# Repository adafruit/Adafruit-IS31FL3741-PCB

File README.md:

## Adafruit IS31FL3741 13x9 PWM RGB LED Matrix Driver PCB

<a href="http://www.adafruit.com/products/5201"><br/>
Click here to purchase one from the Adafruit shop</a>

PCB files for the Adafruit IS31FL3741 13x9 PWM RGB LED Matrix Driver. 

Format is EagleCAD schematic and board layout
* https://www.adafruit.com/product/5201

### Description

Add a splash of RGB LEDs to a project you're working on, with this adorable 13x9 RGB LED matrix breakout. It features -- no surprise -- 117 RGB LEDs, each one 2x2mm in size, in a 13x9 grid with 3mm pitch spacing.

Unlike our 8x8 dotstar grid here, these are not NeoPixel or DotStar or other 'smart' RGB LEDs. Instead of having a lil chip in each LED, there's one large controller chip that handles all the PWM for you. The ISSI IS32FL3741 communicates over I2C and can set each LED element with 8 bit PWM for 24-bit color across the RGB elements, for beautiful color! There's an adjustable current driver so you can brighten or dim the whole display without losing color resolution.

Each assembled board comes with the grid, four mounting holes, and the IS31FL3741 chip with all supporting circuitry. The board can run from 3.3 to 5V DC power and logic - powering from 5V is recommended since the green and blue LEDs look better with the extra headroom. We designed the PCB so you can tile the boards side-to-side if you desire, you'll just have to cut/solder the jumpers on the bottom to change the I2C address: Up to 4 boards can share one I2C bus.

Use Arduino or CircuitPython/Python to quickly set pixels to any color you desire. Note that I2C makes this board very easy to wire up compared to our "HUB75"-style RGB LED Matrices but that also makes the display slower because each pixel must be written over I2C. For a small display with simple animations, its fine - but if you want to do video or larger graphics we recommend upgrading to the HUB75 style.

We made it easy for you to get some color right into your next project. The LED matrix and circuitry is soldered onto a custom-made PCB with two STEMMA QT connectors on the top, and are compatible with the SparkFun Qwiic I2C connectors. This allows you to make solderless connections between your development board and the IS31FL3741 or to chain it with a wide range of other sensors and accessories using a compatible cable.

### License

Adafruit invests time and resources providing this open source design, please support Adafruit and open-source hardware by purchasing products from [Adafruit](https://www.adafruit.com)!

Designed by Limor Fried/Ladyada for Adafruit Industries.

Creative Commons Attribution/Share-Alike, all text above must be included in any redistribution. 
See license.txt for additional details.

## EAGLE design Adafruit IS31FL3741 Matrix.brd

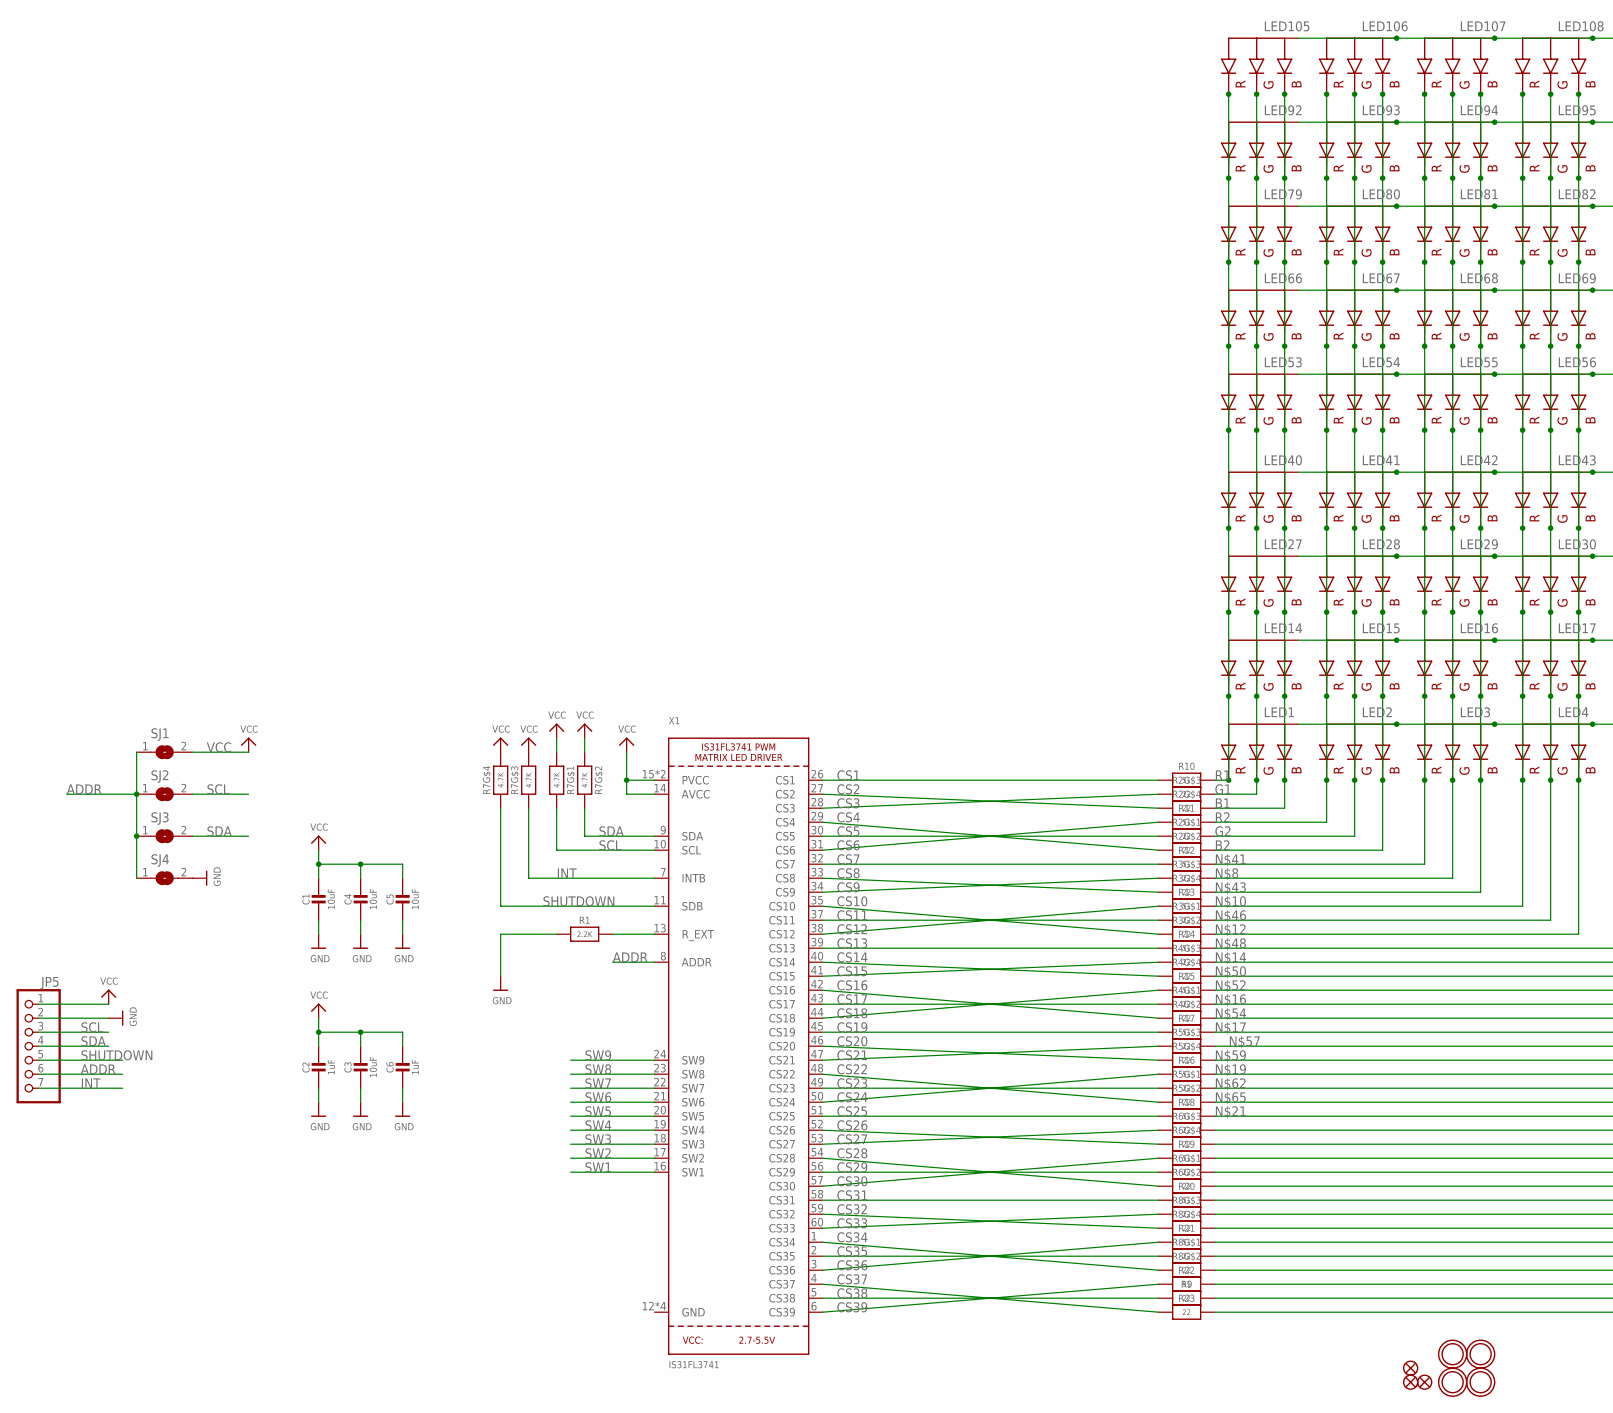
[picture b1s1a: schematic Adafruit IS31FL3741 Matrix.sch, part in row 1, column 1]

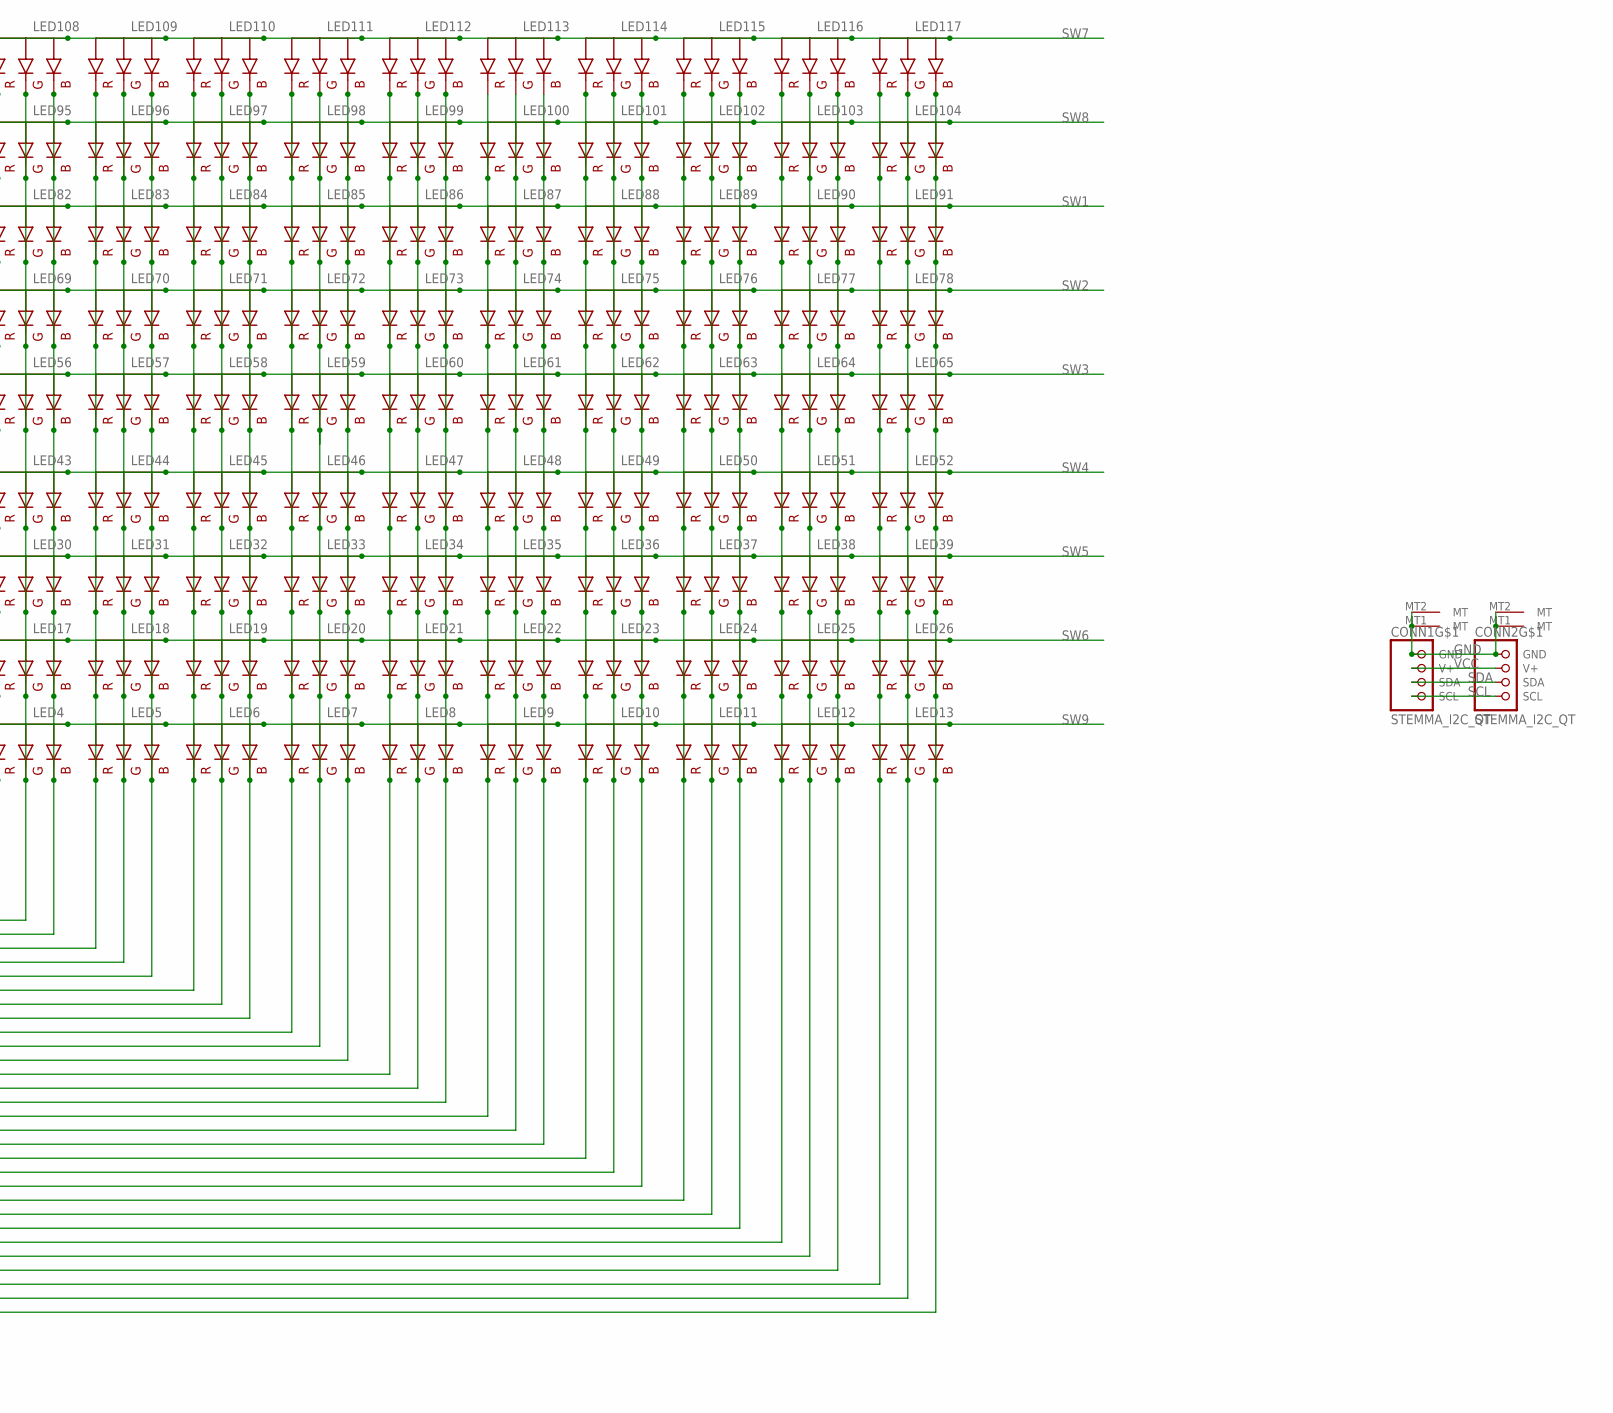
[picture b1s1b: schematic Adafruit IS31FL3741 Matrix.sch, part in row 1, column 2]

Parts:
C1, C3, C4, C5: 10uF; 0805-NO
C2, C6: 1uF; 0603-NO
CONN1, CONN2: STEMMA_I2C_QT; JST_SH4
FID1, FID2, FID3: FIDUCIAL_1MM
JP5: HEADER-1X7THICKER; 1X07_ROUND_76
LED1, LED2, LED3, LED4, LED5, LED6, LED7, LED8, LED9, LED10, LED11, LED12, LED13, LED14, LED15, LED16, LED17, LED18, LED19, LED20, LED21, LED22, LED23, LED24, LED25, LED26, LED27, LED28, LED29, LED30, LED31, LED32, LED33, LED34, LED35, LED36, LED37, LED38, LED39, LED40, LED41, LED42, LED43, LED44, LED45, LED46, LED47, LED48, LED49, LED50, LED51, LED52, LED53, LED54, LED55, LED56, LED57, LED58, LED59, LED60, LED61, LED62, LED63, LED64, LED65, LED66, LED67, LED68, LED69, LED70, LED71, LED72, LED73, LED74, LED75, LED76, LED77, LED78, LED79, LED80, LED81, LED82, LED83, LED84, LED85, LED86, LED87, LED88, LED89, LED90, LED91, LED92, LED93, LED94, LED95, LED96, LED97, LED98, LED99, LED100, LED101, LED102, LED103, LED104, LED105, LED106, LED107, LED108, LED109, LED110, LED111, LED112, LED113, LED114, LED115, LED116, LED117: RGBLED_CA_2121; RGBLED_2121
R1: 2.2K; 0603-NO
R2, R3, R4, R5, R6, R8: 22; RESPACK_4X0603
R7: 4.7K; RESPACK_4X0603
R9, R23: 22; 0603-NO
R10, R11, R12, R13, R14, R15, R16, R17, R18, R19, R20, R21, R22: 51; 0603-NO
SJ1, SJ2, SJ3: SOLDERJUMPER; SOLDERJUMPER_ARROW_NOPASTE
SJ4: SOLDERJUMPERCLOSED; SOLDERJUMPER_CLOSEDWIRE
U$3, U$4, U$5, U$6: MOUNTINGHOLE2.5; MOUNTINGHOLE_2.5_PLATED
X1: IS31FL3741; QFN60_7MM

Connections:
ADDR: JP5.6, SJ1.1, SJ2.1, SJ3.1, SJ4.1, X1.8 (ADDR)
B1: LED1.B (BLUE), LED14.B (BLUE), LED27.B (BLUE), LED40.B (BLUE), LED53.B (BLUE), LED66.B (BLUE), LED79.B (BLUE), LED92.B (BLUE), LED105.B (BLUE), R2.5 (2)
B2: LED2.B (BLUE), LED15.B (BLUE), LED28.B (BLUE), LED41.B (BLUE), LED54.B (BLUE), LED67.B (BLUE), LED80.B (BLUE), LED93.B (BLUE), LED106.B (BLUE), R2.7 (2)
CS1: R10.1, X1.26 (CS1)
CS2: R2.4 (1), X1.27 (CS2)
CS3: R2.3 (1), X1.28 (CS3)
CS4: R2.2 (1), X1.29 (CS4)
CS5: R2.1, X1.30 (CS5)
CS6: R11.1, X1.31 (CS6)
CS7: R12.1, X1.32 (CS7)
CS8: R3.4 (1), X1.33 (CS8)
CS9: R3.3 (1), X1.34 (CS9)
CS10: R3.2 (1), X1.35 (CS10)
CS11: R3.1, X1.37 (CS11)
CS12: R13.1, X1.38 (CS12)
CS13: R14.1, X1.39 (CS13)
CS14: R4.4 (1), X1.40 (CS14)
CS15: R4.3 (1), X1.41 (CS15)
CS16: R4.2 (1), X1.42 (CS16)
CS17: R4.1, X1.43 (CS17)
CS18: R15.1, X1.44 (CS18)
CS19: R17.1, X1.45 (CS19)
CS20: R5.4 (1), X1.46 (CS20)
CS21: R5.3 (1), X1.47 (CS21)
CS22: R5.2 (1), X1.48 (CS22)
CS23: R5.1, X1.49 (CS23)
CS24: R16.1, X1.50 (CS24)
CS25: R18.1, X1.51 (CS25)
CS26: R6.4 (1), X1.52 (CS26)
CS27: R6.3 (1), X1.53 (CS27)
CS28: R6.2 (1), X1.54 (CS28)
CS29: R6.1, X1.56 (CS29)
CS30: R19.1, X1.57 (CS30)
CS31: R20.1, X1.58 (CS31)
CS32: R8.4 (1), X1.59 (CS32)
CS33: R8.3 (1), X1.60 (CS33)
CS34: R8.2 (1), X1.1 (CS34)
CS35: R8.1, X1.2 (CS35)
CS36: R21.1, X1.3 (CS36)
CS37: R23.1, X1.4 (CS37)
CS38: R9.1, X1.5 (CS38)
CS39: R22.1, X1.6 (CS39)
G1: LED1.G (GREEN), LED14.G (GREEN), LED27.G (GREEN), LED40.G (GREEN), LED53.G (GREEN), LED66.G (GREEN), LED79.G (GREEN), LED92.G (GREEN), LED105.G (GREEN), R2.6 (2)
G2: LED2.G (GREEN), LED15.G (GREEN), LED28.G (GREEN), LED41.G (GREEN), LED54.G (GREEN), LED67.G (GREEN), LED80.G (GREEN), LED93.G (GREEN), LED106.G (GREEN), R2.8 (2)
GND: C1.2, C2.2, C3.2, C4.2, C5.2, C6.2, CONN1.1 (GND), CONN1.MT1 (MT), CONN1.MT2 (MT), CONN2.1 (GND), CONN2.MT1 (MT), CONN2.MT2 (MT), JP5.2, R1.1, SJ4.2, X1.12 (GND), X1.36 (GND), X1.55 (GND), X1.THERMAL (GND)
INT: JP5.7, R7.3 (1), X1.7 (INTB)
unnamed: R1.2, X1.13 (R_EXT)
unnamed: LED3.G (GREEN), LED16.G (GREEN), LED29.G (GREEN), LED42.G (GREEN), LED55.G (GREEN), LED68.G (GREEN), LED81.G (GREEN), LED94.G (GREEN), LED107.G (GREEN), R3.6 (2)
unnamed: LED4.R (RED), LED17.R (RED), LED30.R (RED), LED43.R (RED), LED56.R (RED), LED69.R (RED), LED82.R (RED), LED95.R (RED), LED108.R (RED), R13.2
unnamed: LED4.B (BLUE), LED17.B (BLUE), LED30.B (BLUE), LED43.B (BLUE), LED56.B (BLUE), LED69.B (BLUE), LED82.B (BLUE), LED95.B (BLUE), LED108.B (BLUE), R3.7 (2)
unnamed: LED5.G (GREEN), LED18.G (GREEN), LED31.G (GREEN), LED44.G (GREEN), LED57.G (GREEN), LED70.G (GREEN), LED83.G (GREEN), LED96.G (GREEN), LED109.G (GREEN), R4.6 (2)
unnamed: LED6.G (GREEN), LED19.G (GREEN), LED32.G (GREEN), LED45.G (GREEN), LED58.G (GREEN), LED71.G (GREEN), LED84.G (GREEN), LED97.G (GREEN), LED110.G (GREEN), R4.8 (2)
unnamed: LED7.R (RED), LED20.R (RED), LED33.R (RED), LED46.R (RED), LED59.R (RED), LED72.R (RED), LED85.R (RED), LED98.R (RED), LED111.R (RED), R17.2
unnamed: LED8.R (RED), LED21.R (RED), LED34.R (RED), LED47.R (RED), LED60.R (RED), LED73.R (RED), LED86.R (RED), LED99.R (RED), LED112.R (RED), R16.2
unnamed: LED9.R (RED), LED22.R (RED), LED35.R (RED), LED48.R (RED), LED61.R (RED), LED74.R (RED), LED87.R (RED), LED100.R (RED), LED113.R (RED), R18.2
unnamed: LED9.B (BLUE), LED22.B (BLUE), LED35.B (BLUE), LED48.B (BLUE), LED61.B (BLUE), LED74.B (BLUE), LED87.B (BLUE), LED100.B (BLUE), LED113.B (BLUE), R6.5 (2)
unnamed: LED10.G (GREEN), LED23.G (GREEN), LED36.G (GREEN), LED49.G (GREEN), LED62.G (GREEN), LED75.G (GREEN), LED88.G (GREEN), LED101.G (GREEN), LED114.G (GREEN), R6.8 (2)
unnamed: LED11.R (RED), LED24.R (RED), LED37.R (RED), LED50.R (RED), LED63.R (RED), LED76.R (RED), LED89.R (RED), LED102.R (RED), LED115.R (RED), R20.2
unnamed: LED11.B (BLUE), LED24.B (BLUE), LED37.B (BLUE), LED50.B (BLUE), LED63.B (BLUE), LED76.B (BLUE), LED89.B (BLUE), LED102.B (BLUE), LED115.B (BLUE), R8.5 (2)
unnamed: LED12.G (GREEN), LED25.G (GREEN), LED38.G (GREEN), LED51.G (GREEN), LED64.G (GREEN), LED77.G (GREEN), LED90.G (GREEN), LED103.G (GREEN), LED116.G (GREEN), R8.8 (2)
unnamed: LED13.R (RED), LED26.R (RED), LED39.R (RED), LED52.R (RED), LED65.R (RED), LED78.R (RED), LED91.R (RED), LED104.R (RED), LED117.R (RED), R22.2
unnamed: LED13.B (BLUE), LED26.B (BLUE), LED39.B (BLUE), LED52.B (BLUE), LED65.B (BLUE), LED78.B (BLUE), LED91.B (BLUE), LED104.B (BLUE), LED117.B (BLUE), R23.2
unnamed: LED3.R (RED), LED16.R (RED), LED29.R (RED), LED42.R (RED), LED55.R (RED), LED68.R (RED), LED81.R (RED), LED94.R (RED), LED107.R (RED), R12.2
unnamed: LED3.B (BLUE), LED16.B (BLUE), LED29.B (BLUE), LED42.B (BLUE), LED55.B (BLUE), LED68.B (BLUE), LED81.B (BLUE), LED94.B (BLUE), LED107.B (BLUE), R3.5 (2)
unnamed: LED4.G (GREEN), LED17.G (GREEN), LED30.G (GREEN), LED43.G (GREEN), LED56.G (GREEN), LED69.G (GREEN), LED82.G (GREEN), LED95.G (GREEN), LED108.G (GREEN), R3.8 (2)
unnamed: LED5.R (RED), LED18.R (RED), LED31.R (RED), LED44.R (RED), LED57.R (RED), LED70.R (RED), LED83.R (RED), LED96.R (RED), LED109.R (RED), R14.2
unnamed: LED5.B (BLUE), LED18.B (BLUE), LED31.B (BLUE), LED44.B (BLUE), LED57.B (BLUE), LED70.B (BLUE), LED83.B (BLUE), LED96.B (BLUE), LED109.B (BLUE), R4.5 (2)
unnamed: LED6.R (RED), LED19.R (RED), LED32.R (RED), LED45.R (RED), LED58.R (RED), LED71.R (RED), LED84.R (RED), LED97.R (RED), LED110.R (RED), R15.2
unnamed: LED6.B (BLUE), LED19.B (BLUE), LED32.B (BLUE), LED45.B (BLUE), LED58.B (BLUE), LED71.B (BLUE), LED84.B (BLUE), LED97.B (BLUE), LED110.B (BLUE), R4.7 (2)
unnamed: LED7.G (GREEN), LED20.G (GREEN), LED33.G (GREEN), LED46.G (GREEN), LED59.G (GREEN), LED72.G (GREEN), LED85.G (GREEN), LED98.G (GREEN), LED111.G (GREEN), R5.6 (2)
unnamed: LED7.B (BLUE), LED20.B (BLUE), LED33.B (BLUE), LED46.B (BLUE), LED59.B (BLUE), LED72.B (BLUE), LED85.B (BLUE), LED98.B (BLUE), LED111.B (BLUE), R5.5 (2)
unnamed: LED8.G (GREEN), LED21.G (GREEN), LED34.G (GREEN), LED47.G (GREEN), LED60.G (GREEN), LED73.G (GREEN), LED86.G (GREEN), LED99.G (GREEN), LED112.G (GREEN), R5.8 (2)
unnamed: LED8.B (BLUE), LED21.B (BLUE), LED34.B (BLUE), LED47.B (BLUE), LED60.B (BLUE), LED73.B (BLUE), LED86.B (BLUE), LED99.B (BLUE), LED112.B (BLUE), R5.7 (2)
unnamed: LED9.G (GREEN), LED22.G (GREEN), LED35.G (GREEN), LED48.G (GREEN), LED61.G (GREEN), LED74.G (GREEN), LED87.G (GREEN), LED100.G (GREEN), LED113.G (GREEN), R6.6 (2)
unnamed: LED10.R (RED), LED23.R (RED), LED36.R (RED), LED49.R (RED), LED62.R (RED), LED75.R (RED), LED88.R (RED), LED101.R (RED), LED114.R (RED), R19.2
unnamed: LED10.B (BLUE), LED23.B (BLUE), LED36.B (BLUE), LED49.B (BLUE), LED62.B (BLUE), LED75.B (BLUE), LED88.B (BLUE), LED101.B (BLUE), LED114.B (BLUE), R6.7 (2)
unnamed: LED11.G (GREEN), LED24.G (GREEN), LED37.G (GREEN), LED50.G (GREEN), LED63.G (GREEN), LED76.G (GREEN), LED89.G (GREEN), LED102.G (GREEN), LED115.G (GREEN), R8.6 (2)
unnamed: LED12.R (RED), LED25.R (RED), LED38.R (RED), LED51.R (RED), LED64.R (RED), LED77.R (RED), LED90.R (RED), LED103.R (RED), LED116.R (RED), R21.2
unnamed: LED12.B (BLUE), LED25.B (BLUE), LED38.B (BLUE), LED51.B (BLUE), LED64.B (BLUE), LED77.B (BLUE), LED90.B (BLUE), LED103.B (BLUE), LED116.B (BLUE), R8.7 (2)
unnamed: LED13.G (GREEN), LED26.G (GREEN), LED39.G (GREEN), LED52.G (GREEN), LED65.G (GREEN), LED78.G (GREEN), LED91.G (GREEN), LED104.G (GREEN), LED117.G (GREEN), R9.2
R1: LED1.R (RED), LED14.R (RED), LED27.R (RED), LED40.R (RED), LED53.R (RED), LED66.R (RED), LED79.R (RED), LED92.R (RED), LED105.R (RED), R10.2
R2: LED2.R (RED), LED15.R (RED), LED28.R (RED), LED41.R (RED), LED54.R (RED), LED67.R (RED), LED80.R (RED), LED93.R (RED), LED106.R (RED), R11.2
SCL: CONN1.4 (SCL), CONN2.4 (SCL), JP5.3, R7.8 (2), SJ2.2, X1.10 (SCL)
SDA: CONN1.3 (SDA), CONN2.3 (SDA), JP5.4, R7.7 (2), SJ3.2, X1.9 (SDA)
SHUTDOWN: JP5.5, R7.4 (1), X1.11 (SDB)
SW1: LED79.A (VCC), LED80.A (VCC), LED81.A (VCC), LED82.A (VCC), LED83.A (VCC), LED84.A (VCC), LED85.A (VCC), LED86.A (VCC), LED87.A (VCC), LED88.A (VCC), LED89.A (VCC), LED90.A (VCC), LED91.A (VCC), X1.16 (SW1)
SW2: LED66.A (VCC), LED67.A (VCC), LED68.A (VCC), LED69.A (VCC), LED70.A (VCC), LED71.A (VCC), LED72.A (VCC), LED73.A (VCC), LED74.A (VCC), LED75.A (VCC), LED76.A (VCC), LED77.A (VCC), LED78.A (VCC), X1.17 (SW2)
SW3: LED53.A (VCC), LED54.A (VCC), LED55.A (VCC), LED56.A (VCC), LED57.A (VCC), LED58.A (VCC), LED59.A (VCC), LED60.A (VCC), LED61.A (VCC), LED62.A (VCC), LED63.A (VCC), LED64.A (VCC), LED65.A (VCC), X1.18 (SW3)
SW4: LED40.A (VCC), LED41.A (VCC), LED42.A (VCC), LED43.A (VCC), LED44.A (VCC), LED45.A (VCC), LED46.A (VCC), LED47.A (VCC), LED48.A (VCC), LED49.A (VCC), LED50.A (VCC), LED51.A (VCC), LED52.A (VCC), X1.19 (SW4)
SW5: LED27.A (VCC), LED28.A (VCC), LED29.A (VCC), LED30.A (VCC), LED31.A (VCC), LED32.A (VCC), LED33.A (VCC), LED34.A (VCC), LED35.A (VCC), LED36.A (VCC), LED37.A (VCC), LED38.A (VCC), LED39.A (VCC), X1.20 (SW5)
SW6: LED14.A (VCC), LED15.A (VCC), LED16.A (VCC), LED17.A (VCC), LED18.A (VCC), LED19.A (VCC), LED20.A (VCC), LED21.A (VCC), LED22.A (VCC), LED23.A (VCC), LED24.A (VCC), LED25.A (VCC), LED26.A (VCC), X1.21 (SW6)
SW7: LED105.A (VCC), LED106.A (VCC), LED107.A (VCC), LED108.A (VCC), LED109.A (VCC), LED110.A (VCC), LED111.A (VCC), LED112.A (VCC), LED113.A (VCC), LED114.A (VCC), LED115.A (VCC), LED116.A (VCC), LED117.A (VCC), X1.22 (SW7)
SW8: LED92.A (VCC), LED93.A (VCC), LED94.A (VCC), LED95.A (VCC), LED96.A (VCC), LED97.A (VCC), LED98.A (VCC), LED99.A (VCC), LED100.A (VCC), LED101.A (VCC), LED102.A (VCC), LED103.A (VCC), LED104.A (VCC), X1.23 (SW8)
SW9: LED1.A (VCC), LED2.A (VCC), LED3.A (VCC), LED4.A (VCC), LED5.A (VCC), LED6.A (VCC), LED7.A (VCC), LED8.A (VCC), LED9.A (VCC), LED10.A (VCC), LED11.A (VCC), LED12.A (VCC), LED13.A (VCC), X1.24 (SW9)
VCC: C1.1, C2.1, C3.1, C4.1, C5.1, C6.1, CONN1.2 (V+), CONN2.2 (V+), JP5.1, R7.1, R7.2 (1), R7.5 (2), R7.6 (2), SJ1.2, X1.14 (AVCC), X1.15 (PVCC), X1.25 (PVCC)

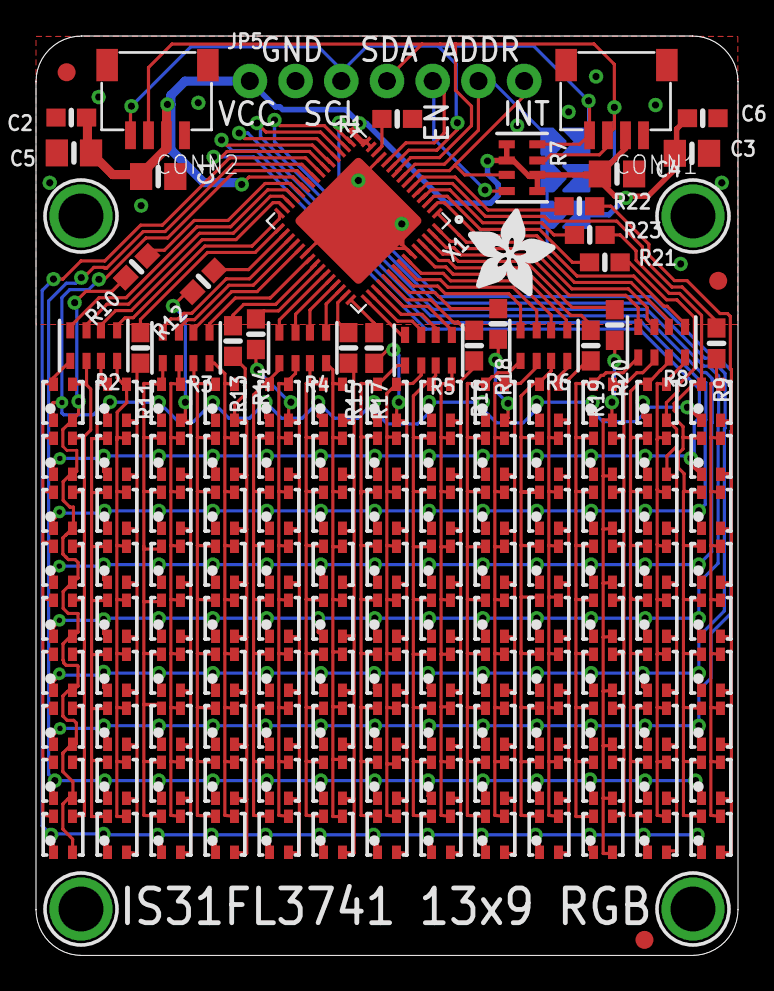
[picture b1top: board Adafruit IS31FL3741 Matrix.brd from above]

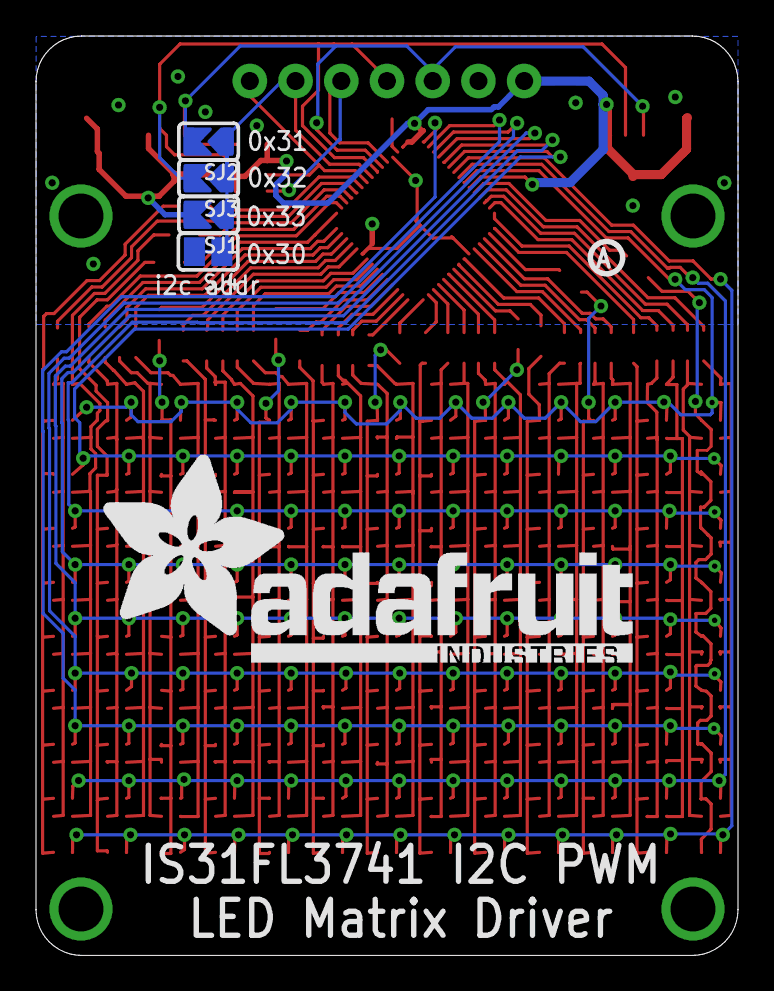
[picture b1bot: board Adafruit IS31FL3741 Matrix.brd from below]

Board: 2 copper layers, 39.0 x 51.1 mm, 164 parts (6 on the bottom side), 95 nets.

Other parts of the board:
U$10: ADAFRUIT_5MM
U$11: PCBFEAT-REV-040
U$16: ADAFRUIT_TEXT_30MM

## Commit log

2021-09-15 Adding board files.

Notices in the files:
parts and their libraries:
microbuilder: This work is placed in the public domain, and may be freely used for commercial and non-commercial work with the following conditions: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
